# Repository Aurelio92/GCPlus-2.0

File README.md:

# GC+ - What is it?
GC+ is a custom board that acts as a Gamecube controller with an upgradable firmware and custom features.
Video reference: https://www.youtube.com/watch?v=MTG2iqWmXx4

# What's new in version 2.0?
* Firmware completely written in C
* Complete controller functionality, including analog triggers and rumble
* Hardware emulation of the GC controller protocol
* Includes a rumble motor driver that supports both LRA and ERM rumble motors
* Additional Z2/ZL button to be used as an extra input for the BT emulation hack
* Compatible with 3DS sliders/Switch sticks without an external converter
* Configurable via homebrew with customizations including:
    * Remappable buttons (except triggers) (via PMv2, coming soon!)
    * Configurable triggers mode between digital and analog, allowing to use both standard triggers and dual---action tacts
    * Completely reconfigurable sticks, both in terms of ranges, and relocation
    * A new deadzone mode allowing for smooth transition across the center of the sticks
* Completely upgradeable!

# How to make one?
Eagle files are available in the Hardware folder. Use them to order PCBs from your favourite manufacturer.

# Needed parts
A BOM is available in the Hardware folder

# How to compile it
GC+2.0 is split in two MPLAB IDE projects. All that you need to do is open GCPlus2.0_Bootloader.X in MPLAB IDE and compile it. GCPlus2.0_Bootloader loads GCPlus2.0 internally. This means that when you compile the bootloader, an unified hex file containing both the bootloader and the main payload firmware. The main firmware project is configured to use a different memory region to avoid overlaps with the bootloader.

# How to flash it
Markup : 
Flash GC+2.0.hex with MPLAB IPE (http://microchip.wikidot.com/ipe:installation) and a PICKIT v3 (or above).
Use the above pinout to wire up GC+2.0 to your PICKIT.

# Contacts
Please if you have any questions or if you want to implement new features reach out to me (Aurelio) on BitBuilt.net forums or our Discord server at https://discordapp.com/invite/uwT2AC.

If you use GC+2.0 and/or integrate it in your own project please do not forget to give credits where due and link to this repository.

# License

MIT License

Copyright (c) 2020 Aurelio Mannara

Permission is hereby granted, free of charge, to any person obtaining a copy
of this software and associated documentation files (the "Software"), to deal
in the Software without restriction, including without limitation the rights
to use, copy, modify, merge, publish, distribute, sublicense, and/or sell
copies of the Software, and to permit persons to whom the Software is
furnished to do so, subject to the following conditions:

The above copyright notice and this permission notice shall be included in all
copies or substantial portions of the Software.

THE SOFTWARE IS PROVIDED "AS IS", WITHOUT WARRANTY OF ANY KIND, EXPRESS OR
IMPLIED, INCLUDING BUT NOT LIMITED TO THE WARRANTIES OF MERCHANTABILITY,
FITNESS FOR A PARTICULAR PURPOSE AND NONINFRINGEMENT. IN NO EVENT SHALL THE
AUTHORS OR COPYRIGHT HOLDERS BE LIABLE FOR ANY CLAIM, DAMAGES OR OTHER
LIABILITY, WHETHER IN AN ACTION OF CONTRACT, TORT OR OTHERWISE, ARISING FROM,
OUT OF OR IN CONNECTION WITH THE SOFTWARE OR THE USE OR OTHER DEALINGS IN THE
SOFTWARE.E, ARISING FROM,
OUT OF OR IN CONNECTION WITH THE SOFTWARE OR THE USE OR OTHER DEALINGS IN THE
SOFTWARE.

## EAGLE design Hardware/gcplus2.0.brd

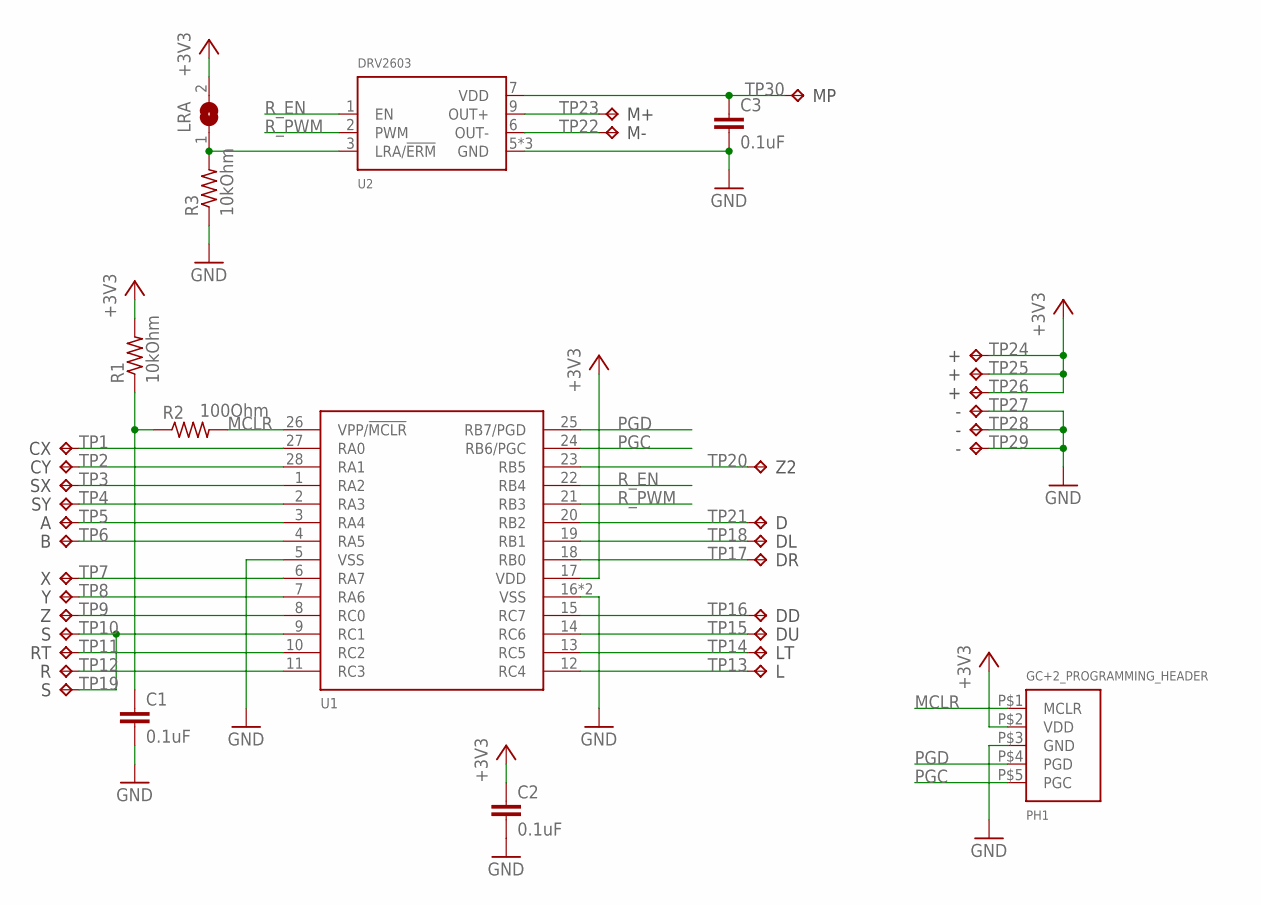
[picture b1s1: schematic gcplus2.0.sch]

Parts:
C1, C2, C3: 0.1uF; C0402
LRA: SJ
PH1: GC+2_PROGRAMMING_HEADER
R1, R3: 10kOhm; R0402
R2: 100Ohm; R0402
TP1, TP2, TP3, TP4, TP5, TP6, TP7, TP8, TP9, TP10, TP11, TP12, TP13, TP14, TP15, TP16, TP17, TP18, TP19, TP20, TP21, TP22, TP23, TP24, TP25, TP26, TP27, TP28, TP29, TP30: TPTP10SQ; TP10SQ
U1: PIC18F25K42; QFN-28
U2: DRV2603; WQFN-10

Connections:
+3V3: C2.1, LRA.2, PH1.P$2 (VDD), R1.2, TP24.TP, TP25.TP, TP26.TP, U1.17 (VDD)
GND: C1.2, C2.2, C3.2, PH1.P$3 (GND), R3.1, TP27.TP, TP28.TP, TP29.TP, U1.5 (VSS), U1.16 (VSS), U1.PAD (VSS), U2.5 (GND), U2.8 (GND), U2.10 (GND)
MCLR: PH1.P$1 (MCLR), R2.2, U1.26 (VPP/!MCLR)
MP: C3.1, TP30.TP, U2.7 (VDD)
unnamed: TP1.TP, U1.27 (RA0)
unnamed: TP2.TP, U1.28 (RA1)
unnamed: TP3.TP, U1.1 (RA2)
unnamed: TP4.TP, U1.2 (RA3)
unnamed: TP5.TP, U1.3 (RA4)
unnamed: TP6.TP, U1.4 (RA5)
unnamed: TP7.TP, U1.6 (RA7)
unnamed: TP8.TP, U1.7 (RA6)
unnamed: TP9.TP, U1.8 (RC0)
unnamed: LRA.1, R3.2, U2.3 (LRA/!ERM)
unnamed: TP10.TP, TP19.TP, U1.9 (RC1)
unnamed: TP11.TP, U1.10 (RC2)
unnamed: TP12.TP, U1.11 (RC3)
unnamed: TP14.TP, U1.13 (RC5)
unnamed: TP15.TP, U1.14 (RC6)
unnamed: TP16.TP, U1.15 (RC7)
unnamed: TP17.TP, U1.18 (RB0)
unnamed: TP18.TP, U1.19 (RB1)
unnamed: TP21.TP, U1.20 (RB2)
unnamed: TP23.TP, U2.9 (OUT+)
unnamed: TP22.TP, U2.6 (OUT-)
unnamed: TP20.TP, U1.23 (RB5)
unnamed: C1.1, R1.1, R2.1
unnamed: TP13.TP, U1.12 (RC4)
PGC: PH1.P$5 (PGC), U1.24 (RB6/PGC)
PGD: PH1.P$4 (PGD), U1.25 (RB7/PGD)
R_EN: U1.22 (RB4), U2.1 (EN)
R_PWM: U1.21 (RB3), U2.2 (PWM)

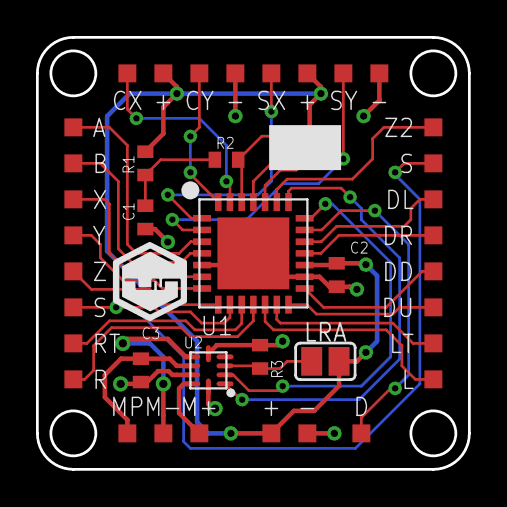
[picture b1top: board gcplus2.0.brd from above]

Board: 2 copper layers, 24.0 x 24.0 mm, 40 parts (0 on the bottom side), 32 nets.

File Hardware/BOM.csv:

"Qty";"Value";"Device";"Package";"Parts";"Description";
"3";"0.1uF";"C-EUC0402";"C0402";"C1, C2, C3";"CAPACITOR, European symbol";
"2";"10kOhm";"R-US_R0402";"R0402";"R1, R3";"RESISTOR, American symbol";
"1";"100Ohm";"R-US_R0402";"R0402";"R2";"RESISTOR, American symbol";
"1";"PIC18F25K42";"PIC18F25K42";"QFN-28";"U1";"";
"1";"DRV2603";"DRV2603";"WQFN-10";"U2";"";

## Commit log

2019-10-24 Created boot loader project
2019-10-24 Update configuration registers
2019-10-29 Completed boot loader code
2019-10-29 Added check for header in bootloader
2019-10-29 Implemented rumble functions
2019-10-30 Handled deadzone modes
2019-11-03 Implemented buttons mapping
2019-11-03 Implemented rumble
2019-11-04 Fixed LUT generation
2019-11-04 Implemented getmap commands
2019-11-04 Fixed buttons mapping
2019-11-04 Added time diagram plot script
2019-11-04 Fixed rumble
2019-11-05 Started GCPlus configurator
2019-11-06 Animation class
2019-11-06 Updated payload code and cleaned up the code
2019-11-06 Made progress on animation class
2019-11-13 Made the configurator dependent on libBBGUI
2019-11-18 Made payload able to boot back to boot loader
2019-11-20 Added protocol pics
2019-12-12 Fixed triggers
2021-04-01 Version 2.2
2023-03-22 Version 2.3 Fixed issues with rumble
2023-03-22 Fixed readme and LICENSE file
2023-03-23 Added back Firmware and Hardware folders
2024-11-10 Update to version 2.4. Implemented configurable triggers ranges
2025-04-26 Resolve bug causing left stick X values to glitch
    When the left stick is moved in some patterns, such as released from
    being held fully to the right and quickly moving back to the center,
    or moving from the center quickly to the right, the `ADC_SX` value
    would glitch and show the stick as being as far to the left (0 value)
    as possible. This was not reflective of reality.
    While the cause of this bug is not known, this commit fixes the issue
